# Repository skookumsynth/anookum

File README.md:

# Anookum

The Anookum is a derivative of Olivier Gillet's "Anushri" monophonic synthesizer.

https://github.com/pichenettes/anushri

It uses alternate parts to make sourcing easier for users in North America.
Files are licensed as per the original CC-BY-SA 3.0 license.

No warranties provided.
www.skookumsynth.com

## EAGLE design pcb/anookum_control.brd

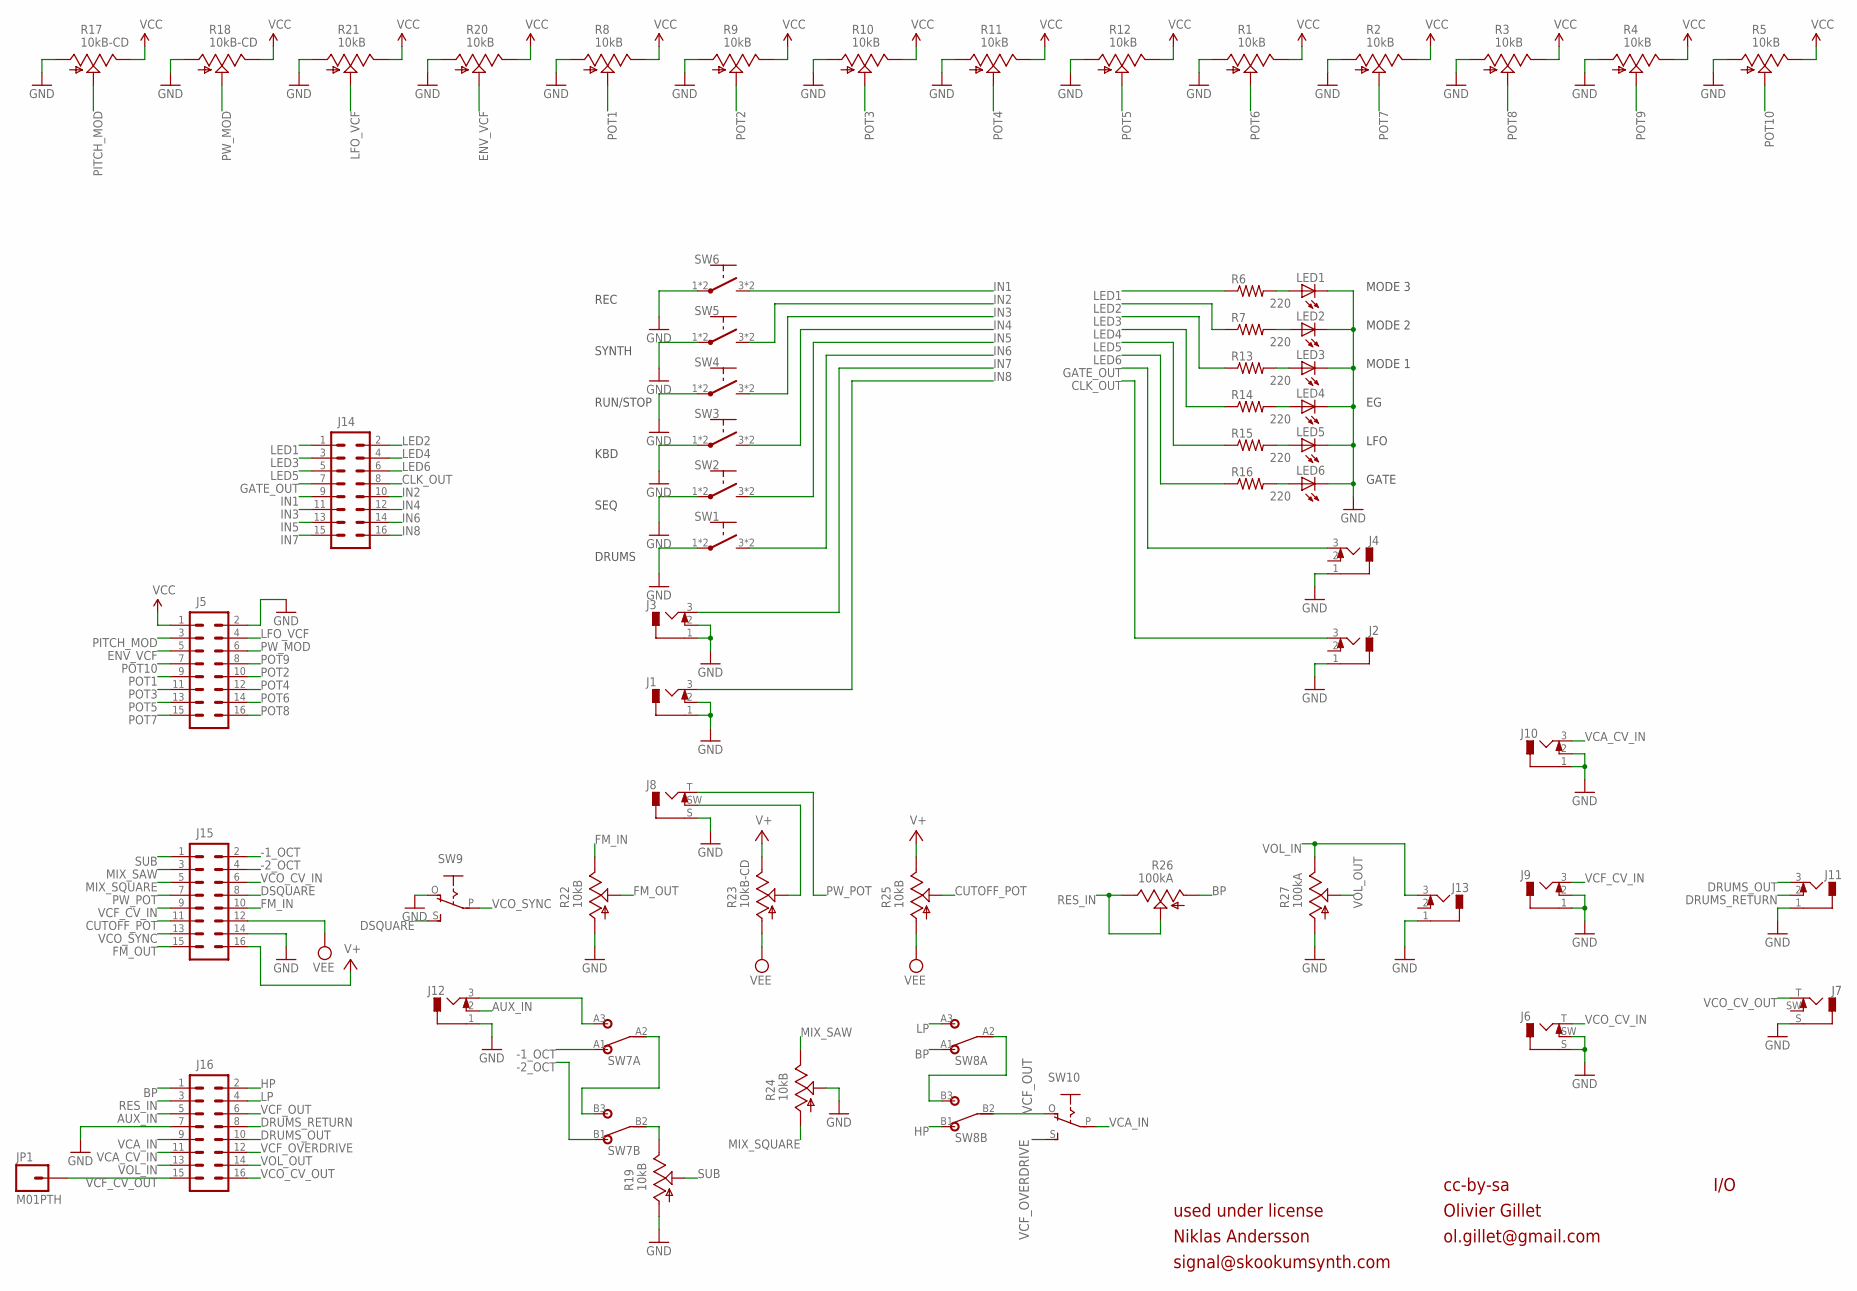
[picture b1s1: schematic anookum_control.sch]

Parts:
J1, J2, J3, J4, J9, J10, J11, J12, J13: JACK_MONO_SW_V; WQP_PJ301M-12@1
J5, J14, J15, J16: M08X2; 2X8
J6, J7, J8: CONN_MONO_SW_F_V; WQP_PJ301M-12
JP1: M01PTH; 1X01
LED1, LED2, LED3, LED4, LED5, LED6: LED3MM
R1, R2, R3, R4, R5, R8, R9, R10, R11, R12, R19, R20, R21, R22, R24, R25: 10kB; ALPS_POT_VERTICAL
R6, R7, R13, R14, R15, R16: 220; 0204/7
R17, R18, R23: 10kB-CD; ALPS_POT_VERTICAL
R26, R27: 100kA; ALPS_POT_VERTICAL
SW1, SW2, SW3, SW4, SW5, SW6: SW_TACTD6; D6
SW7, SW8: DPDT1AD6T2B4M2RE; DPDT
SW9, SW10: EG1218S; EG1218

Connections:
-1_OCT: J15.2, SW7.A1 (1)
-2_OCT: J15.4, SW7.B1 (1)
AUX_IN: J12.2 (SW), J16.5
BP: J16.1, R26.P$3 (A), SW8.A1 (1)
CLK_OUT: J2.3 (T), J14.8
CUTOFF_POT: J15.11, R25.P$2 (S)
DRUMS_OUT: J11.3 (T), J16.10
DRUMS_RETURN: J11.2 (SW), J16.8
DSQUARE: J15.8, SW9.S
ENV_VCF: J5.5, R20.P$2 (S)
FM_IN: J15.10, R22.P$1 (E)
FM_OUT: J15.15, R22.P$2 (S)
GATE_OUT: J4.3 (T), J14.7
GND: J1.1 (S), J1.2 (SW), J2.1 (S), J3.1 (S), J3.2 (SW), J4.1 (S), J5.2, J6.S, J6.SW, J7.S, J8.S, J9.1 (S), J9.2 (SW), J10.1 (S), J10.2 (SW), J11.1 (S), J12.1 (S), J13.1 (S), J15.14, J16.7, LED1.K (C), LED2.K (C), LED3.K (C), LED4.K (C), LED5.K (C), LED6.K (C), R1.P$3 (A), R2.P$3 (A), R3.P$3 (A), R4.P$3 (A), R5.P$3 (A), R8.P$3 (A), R9.P$3 (A), R10.P$3 (A), R11.P$3 (A), R12.P$3 (A), R17.P$3 (A), R18.P$3 (A), R19.P$3 (A), R20.P$3 (A), R21.P$3 (A), R22.P$3 (A), R24.P$2 (S), R27.P$3 (A), SW1.1, SW1.2 (1), SW2.1, SW2.2 (1), SW3.1, SW3.2 (1), SW4.1, SW4.2 (1), SW5.1, SW5.2 (1), SW6.1, SW6.2 (1), SW9.O
HP: J16.2, SW8.B1 (1)
IN1: J14.9, SW6.3 (2), SW6.4 (2)
IN2: J14.10, SW5.3 (2), SW5.4 (2)
IN3: J14.11, SW4.3 (2), SW4.4 (2)
IN4: J14.12, SW3.3 (2), SW3.4 (2)
IN5: J14.13, SW2.3 (2), SW2.4 (2)
IN6: J14.14, SW1.3 (2), SW1.4 (2)
IN7: J3.3 (T), J14.15
IN8: J1.3 (T), J14.16
LED1: J14.1, R6.1
LED2: J14.2, R7.1
LED3: J14.3, R13.1
LED4: J14.4, R14.1
LED5: J14.5, R15.1
LED6: J14.6, R16.1
LFO_VCF: J5.4, R21.P$2 (S)
LP: J16.4, SW8.A3 (3)
MIX_SAW: J15.3, R24.P$1 (E)
MIX_SQUARE: J15.5, R24.P$3 (A)
unnamed: J8.SW, R23.P$2 (S)
unnamed: R19.P$1 (E), SW7.B2 (2)
unnamed: J12.3 (T), SW7.A3 (3)
unnamed: SW8.A2 (2), SW8.B3 (3)
unnamed: LED1.A, R6.2
unnamed: LED2.A, R7.2
unnamed: LED3.A, R13.2
unnamed: LED4.A, R14.2
unnamed: LED5.A, R15.2
unnamed: LED6.A, R16.2
unnamed: SW7.A2 (2), SW7.B3 (3)
PITCH_MOD: J5.3, R17.P$2 (S)
POT1: J5.9, R8.P$2 (S)
POT2: J5.10, R9.P$2 (S)
POT3: J5.11, R10.P$2 (S)
POT4: J5.12, R11.P$2 (S)
POT5: J5.13, R12.P$2 (S)
POT6: J5.14, R1.P$2 (S)
POT7: J5.15, R2.P$2 (S)
POT8: J5.16, R3.P$2 (S)
POT9: J5.8, R4.P$2 (S)
POT10: J5.7, R5.P$2 (S)
PW_MOD: J5.6, R18.P$2 (S)
PW_POT: J8.T, J15.7
RES_IN: J16.3, R26.P$1 (E), R26.P$2 (S)
SUB: J15.1, R19.P$2 (S)
V+: J15.16, R23.P$1 (E), R25.P$1 (E)
VCA_CV_IN: J10.3 (T), J16.11
VCA_IN: J16.9, SW10.P
VCC: J5.1, R1.P$1 (E), R2.P$1 (E), R3.P$1 (E), R4.P$1 (E), R5.P$1 (E), R8.P$1 (E), R9.P$1 (E), R10.P$1 (E), R11.P$1 (E), R12.P$1 (E), R17.P$1 (E), R18.P$1 (E), R20.P$1 (E), R21.P$1 (E)
VCF_CV_IN: J9.3 (T), J15.9
VCF_CV_OUT: J16.15, JP1.1
VCF_OUT: J16.6, SW8.B2 (2), SW10.O
VCF_OVERDRIVE: J16.12, SW10.S
VCO_CV_IN: J6.T, J15.6
VCO_CV_OUT: J7.T, J16.16
VCO_SYNC: J15.13, SW9.P
VEE: J15.12, R23.P$3 (A), R25.P$3 (A)
VOL_IN: J13.3 (T), J16.13, R27.P$1 (E)
VOL_OUT: J16.14, R27.P$2 (S)

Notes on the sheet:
LFO
GATE
MODE 1
MODE 2
MODE 3
cc-by-sa
Olivier Gillet
ol.gillet@gmail.com
I/O
KBD
SEQ
SYNTH
RUN/STOP
REC
DRUMS
used under license
Niklas Andersson
signal@skookumsynth.com

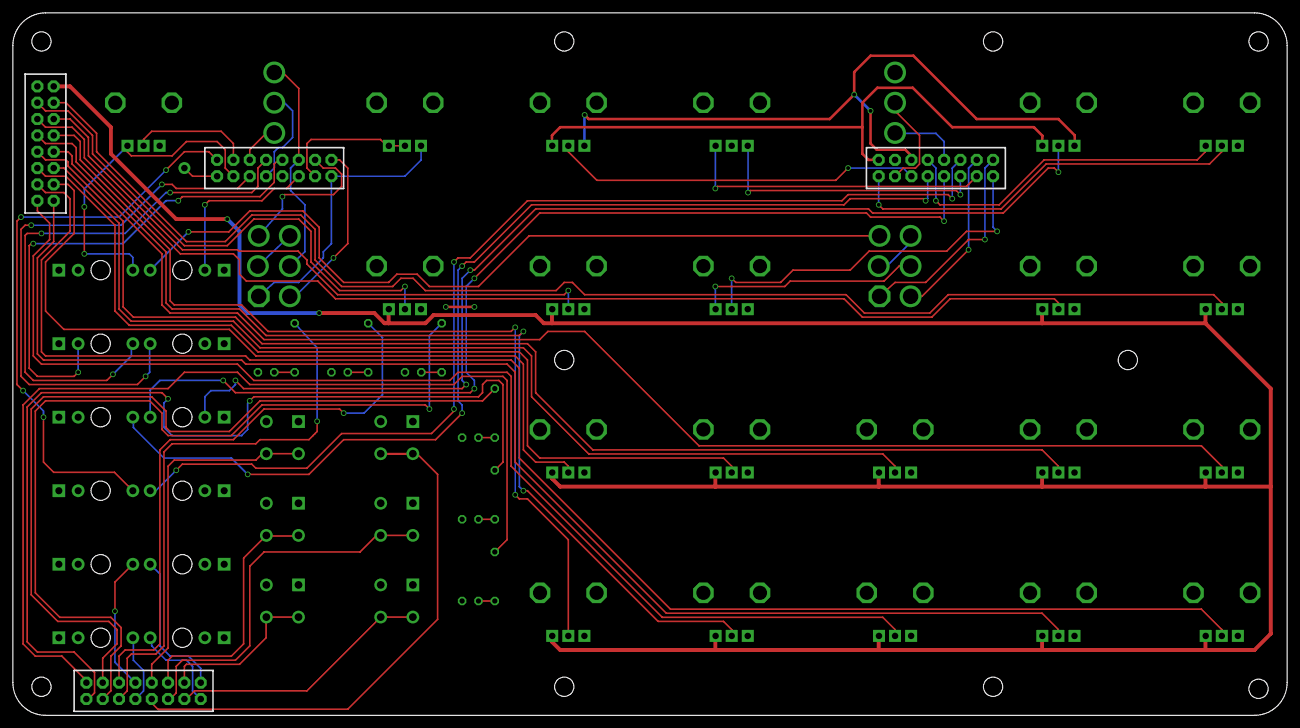
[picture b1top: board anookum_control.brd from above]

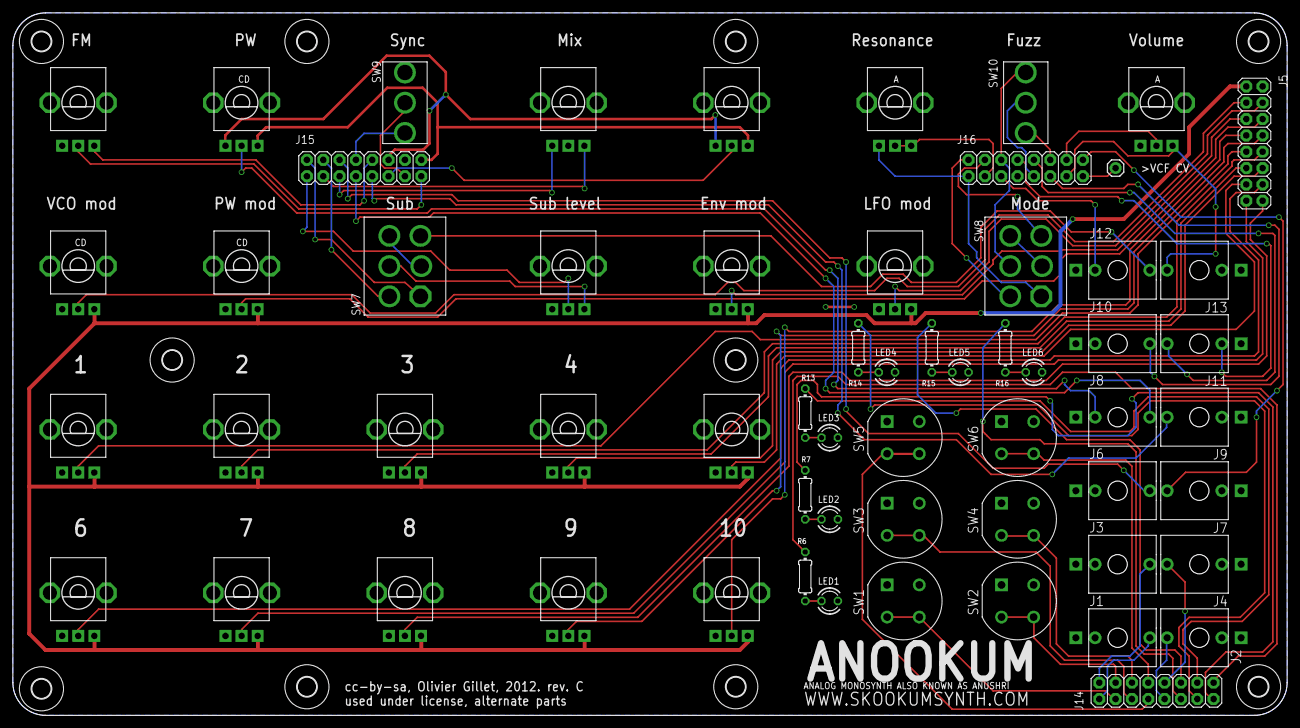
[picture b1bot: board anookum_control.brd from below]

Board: 2 copper layers, 198.1 x 109.2 mm, 70 parts (70 on the bottom side), 73 nets.

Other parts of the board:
U$1, U$2, U$3, U$4, U$6, U$7, U$8, U$9, U$10, U$11: 3,0

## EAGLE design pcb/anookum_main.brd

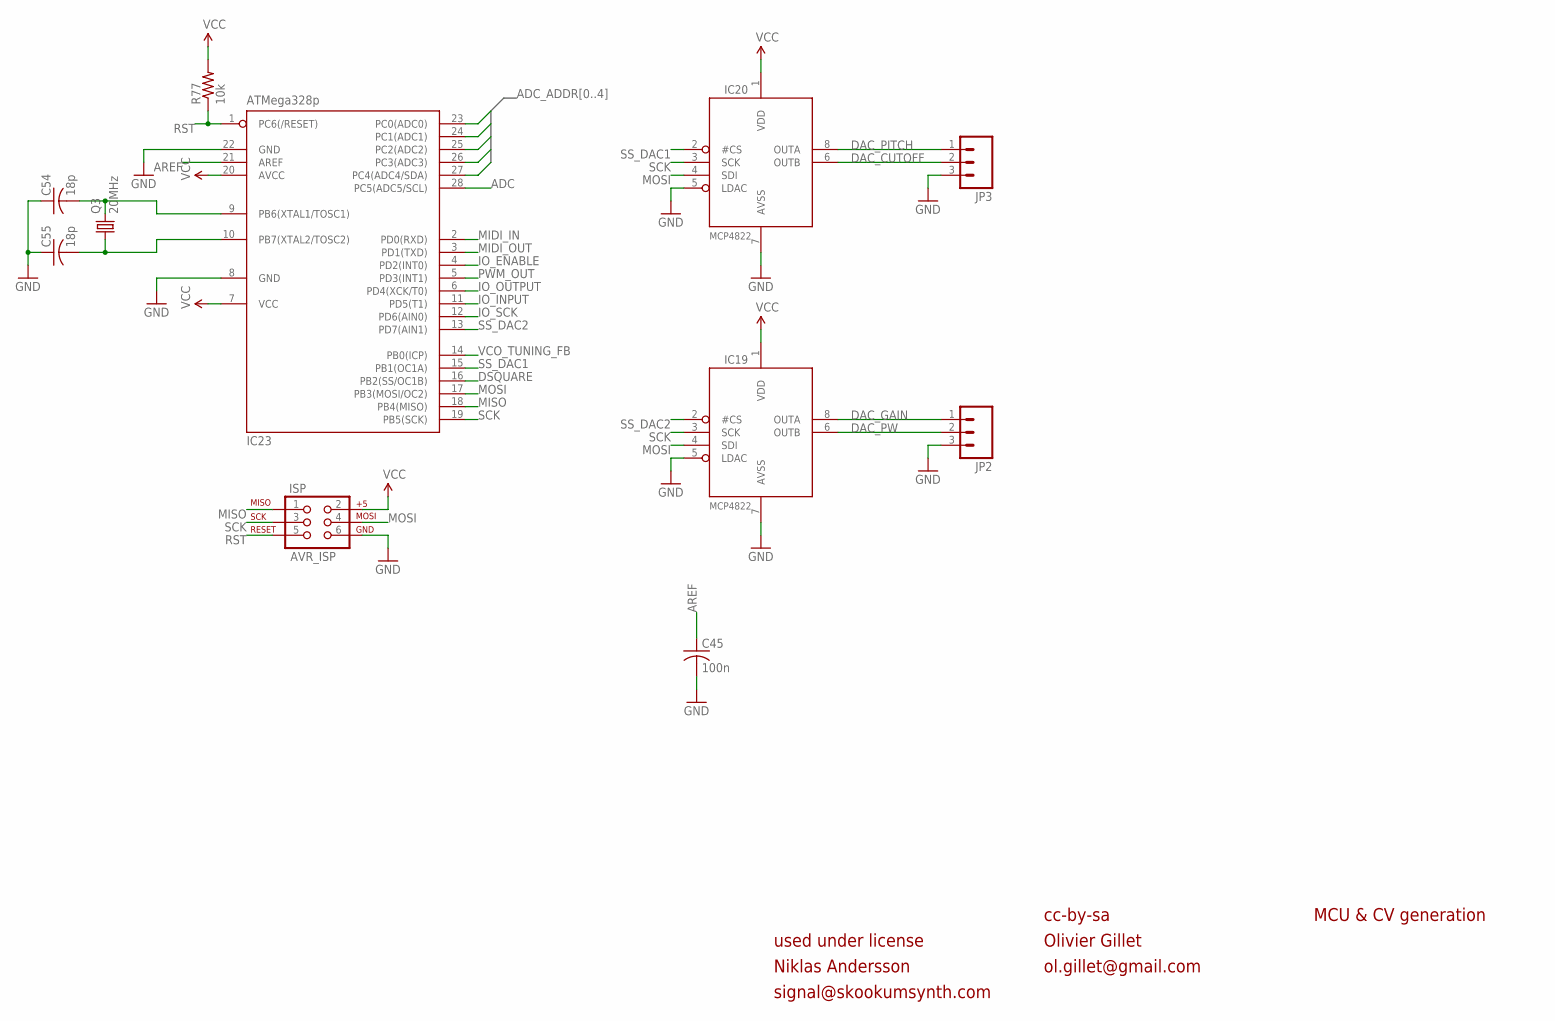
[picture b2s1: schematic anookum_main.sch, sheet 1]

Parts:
C45: 100n; C025-025X050
C54, C55: 18p; C025-025X050
IC19, IC20: MCP4822; DIL08
IC23: ATMega328p; DIL28-3
ISP: AVR_ISP; 2X3
JP2, JP3: M03PTH; 1X03
Q3: 20MHz; HC49U-V
R77: 10k; 0204/7

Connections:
ADC: IC23.28 (PC5(ADC5/SCL)); also elsewhere on the board
ADC_ADDR0: IC23.25 (PC2(ADC2)); also elsewhere on the board
ADC_ADDR1: IC23.24 (PC1(ADC1)); also elsewhere on the board
ADC_ADDR2: IC23.23 (PC0(ADC0)); also elsewhere on the board
ADC_ADDR3: IC23.26 (PC3(ADC3)); also elsewhere on the board
ADC_ADDR4: IC23.27 (PC4(ADC4/SDA)); also elsewhere on the board
AREF: C45.1, IC23.21 (AREF)
DAC_CUTOFF: IC20.6 (OUTB), JP3.2; also elsewhere on the board
DAC_GAIN: IC19.8 (OUTA), JP2.1; also elsewhere on the board
DAC_PITCH: IC20.8 (OUTA), JP3.1; also elsewhere on the board
DAC_PW: IC19.6 (OUTB), JP2.2; also elsewhere on the board
DSQUARE: IC23.16 (PB2(SS/OC1B)); also elsewhere on the board
GND: C45.2, C54.1, C55.1, IC19.5 (LDAC), IC19.7 (AVSS), IC20.5 (LDAC), IC20.7 (AVSS), IC23.8 (GND), IC23.22 (GND), ISP.6, JP2.3, JP3.3; also elsewhere on the board
IO_ENABLE: IC23.4 (PD2(INT0)); also elsewhere on the board
IO_INPUT: IC23.11 (PD5(T1)); also elsewhere on the board
IO_OUTPUT: IC23.6 (PD4(XCK/T0)); also elsewhere on the board
IO_SCK: IC23.12 (PD6(AIN0)); also elsewhere on the board
MIDI_IN: IC23.2 (PD0(RXD)); also elsewhere on the board
MIDI_OUT: IC23.3 (PD1(TXD)); also elsewhere on the board
MISO: IC23.18 (PB4(MISO)), ISP.1
MOSI: IC19.4 (SDI), IC20.4 (SDI), IC23.17 (PB3(MOSI/OC2)), ISP.4
unnamed: C55.2, IC23.10 (PB7(XTAL2/TOSC2)), Q3.1
unnamed: C54.2, IC23.9 (PB6(XTAL1/TOSC1)), Q3.2
PWM_OUT: IC23.5 (PD3(INT1)); also elsewhere on the board
RST: IC23.1 (PC6(/RESET)), ISP.5, R77.1
SCK: IC19.3 (SCK), IC20.3 (SCK), IC23.19 (PB5(SCK)), ISP.3
SS_DAC1: IC20.2 (#CS), IC23.15 (PB1(OC1A))
SS_DAC2: IC19.2 (#CS), IC23.13 (PD7(AIN1))
VCC: IC19.1 (VDD), IC20.1 (VDD), IC23.7 (VCC), IC23.20 (AVCC), ISP.2, R77.2; also elsewhere on the board
VCO_TUNING_FB: IC23.14 (PB0(ICP)); also elsewhere on the board

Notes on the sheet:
cc-by-sa
Olivier Gillet
ol.gillet@gmail.com
MCU & CV generation
used under license
Niklas Andersson
signal@skookumsynth.com

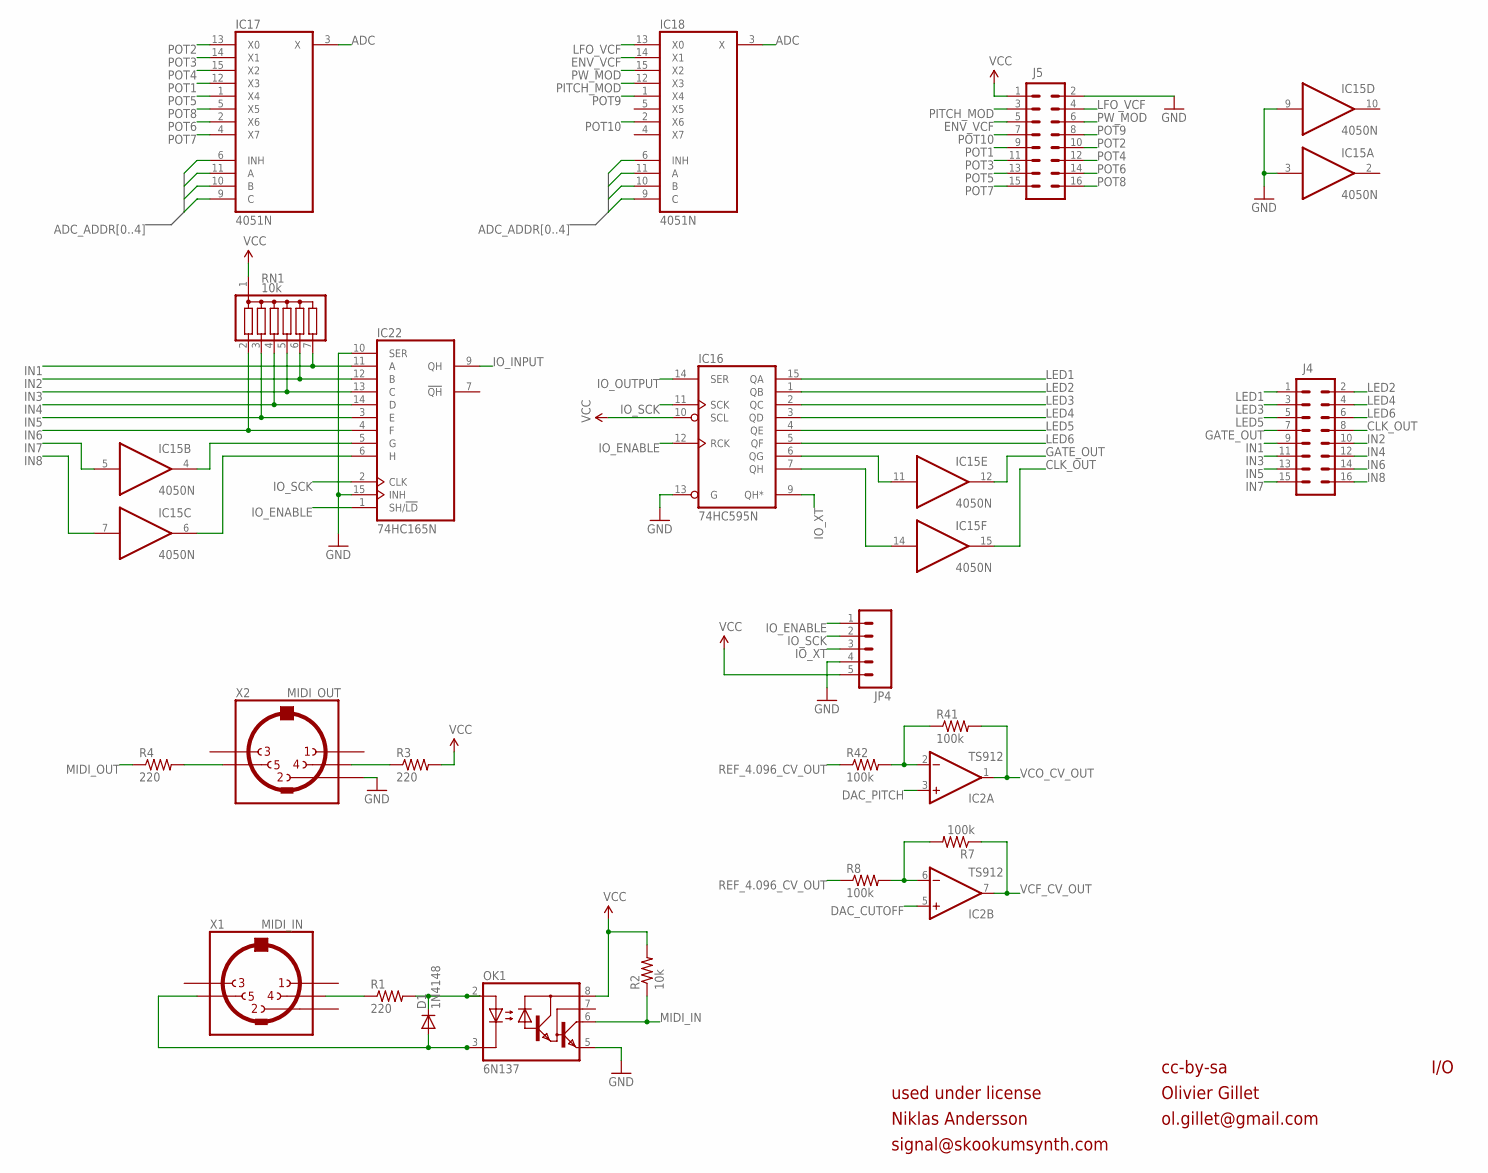
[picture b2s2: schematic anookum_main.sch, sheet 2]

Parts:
D1: 1N4148; D-5
IC2: TS912; DIL08
IC15: 4050N; DIL16
IC16: 74HC595N; DIL16
IC17, IC18: 4051N; DIL16
IC22: 74HC165N; DIL16
J4, J5: M08X2; 2X8
JP4: M05PTH; 1X05
OK1: 6N137; DIL08
R1, R3, R4: 220; 0204/7
R2: 10k; 0204/7
R7, R8, R41, R42: 100k; 0204/7
RN1: 10k; SIL7
X1: MIDI_IN; SDS-50J
X2: MIDI_OUT; SDS-50J

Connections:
ADC: IC17.3 (X), IC18.3 (X); also elsewhere on the board
ADC_ADDR0: IC17.11 (A), IC18.11 (A); also elsewhere on the board
ADC_ADDR1: IC17.10 (B), IC18.10 (B); also elsewhere on the board
ADC_ADDR2: IC17.9 (C), IC18.9 (C); also elsewhere on the board
ADC_ADDR3: IC17.6 (INH); also elsewhere on the board
ADC_ADDR4: IC18.6 (INH); also elsewhere on the board
CLK_OUT: IC15.15 (O), J4.8
DAC_CUTOFF: IC2.5 (+IN); also elsewhere on the board
DAC_PITCH: IC2.3 (+IN); also elsewhere on the board
ENV_VCF: IC18.14 (X1), J5.5
GATE_OUT: IC15.12 (O), J4.7
GND: IC15.3 (I), IC15.9 (I), IC16.13 (G), IC22.10 (SER), IC22.15 (INH), J5.2, JP4.4, OK1.5 (GND), X2.2; also elsewhere on the board
IN1: IC22.11 (A), J4.9, RN1.7
IN2: IC22.12 (B), J4.10, RN1.6
IN3: IC22.13 (C), J4.11, RN1.5
IN4: IC22.14 (D), J4.12, RN1.4
IN5: IC22.3 (E), J4.13, RN1.3
IN6: IC22.4 (F), J4.14, RN1.2
IN7: IC15.5 (I), J4.15
IN8: IC15.7 (I), J4.16
IO_ENABLE: IC16.12 (RCK), IC22.1 (SH/!LD), JP4.1; also elsewhere on the board
IO_INPUT: IC22.9 (QH); also elsewhere on the board
IO_OUTPUT: IC16.14 (SER); also elsewhere on the board
IO_SCK: IC16.11 (SCK), IC22.2 (CLK), JP4.2; also elsewhere on the board
IO_XT: IC16.9 (QH*), JP4.3
LED1: IC16.15 (QA), J4.1
LED2: IC16.1 (QB), J4.2
LED3: IC16.2 (QC), J4.3
LED4: IC16.3 (QD), J4.4
LED5: IC16.4 (QE), J4.5
LED6: IC16.5 (QF), J4.6
LFO_VCF: IC18.13 (X0), J5.4
MIDI_IN: OK1.6 (VO), R2.1; also elsewhere on the board
MIDI_IN4: R1.1, X1.4
MIDI_IN5: D1.A, OK1.3 (C), X1.5
MIDI_OUT: R4.1; also elsewhere on the board
MIDI_OUT3: R3.1, X2.4
MIDI_OUT5: R4.2, X2.5
unnamed: IC15.11 (I), IC16.6 (QG)
unnamed: IC15.14 (I), IC16.7 (QH)
unnamed: D1.C, OK1.2 (A), R1.2
unnamed: IC15.4 (O), IC22.5 (G)
unnamed: IC15.6 (O), IC22.6 (H)
unnamed: IC2.2 (-IN), R41.1, R42.2
unnamed: IC2.6 (-IN), R7.2, R8.2
PITCH_MOD: IC18.12 (X3), J5.3
POT1: IC17.12 (X3), J5.9
POT2: IC17.13 (X0), J5.10
POT3: IC17.14 (X1), J5.11
POT4: IC17.15 (X2), J5.12
POT5: IC17.1 (X4), J5.13
POT6: IC17.2 (X6), J5.14
POT7: IC17.4 (X7), J5.15
POT8: IC17.5 (X5), J5.16
POT9: IC18.1 (X4), J5.8
POT10: IC18.2 (X6), J5.7
PW_MOD: IC18.15 (X2), J5.6
REF_4.096_CV_OUT: R8.1, R42.1; also elsewhere on the board
VCC: IC16.10 (SCL), J5.1, JP4.5, OK1.8 (VCC), R2.2, R3.2, RN1.1; also elsewhere on the board
VCF_CV_OUT: IC2.7 (OUT), R7.1; also elsewhere on the board
VCO_CV_OUT: IC2.1 (OUT), R41.2; also elsewhere on the board

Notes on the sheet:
cc-by-sa
Olivier Gillet
ol.gillet@gmail.com
I/O
used under license
Niklas Andersson
signal@skookumsynth.com

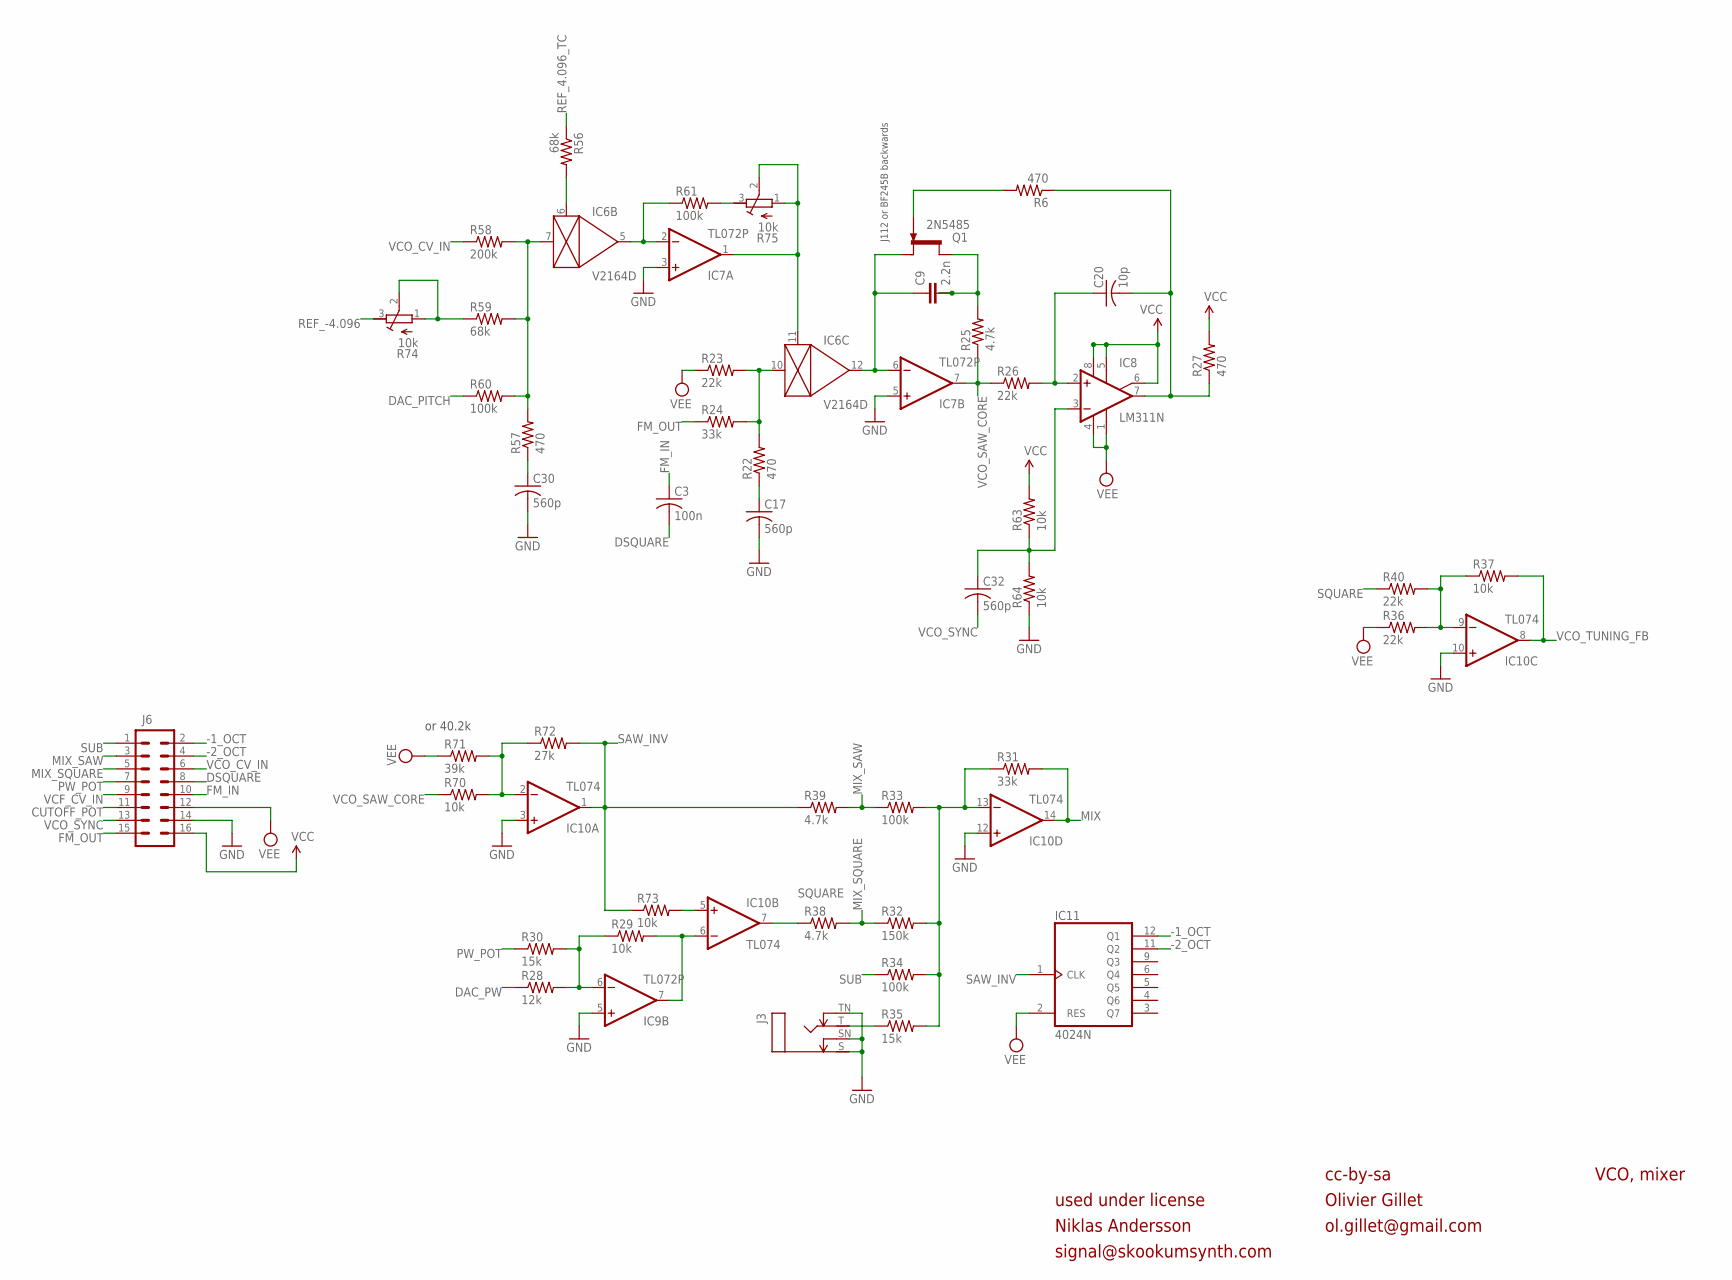
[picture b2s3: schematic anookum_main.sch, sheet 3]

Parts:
C3: 100n; C025-025X050
C9: 2.2n; C2.5/5-5
C17, C30, C32: 560p; C025-025X050
C20: 10p; C025-025X050
IC6: V2164D; DIL16
IC7, IC9: TL072P; DIL08
IC8: LM311N; DIL08
IC10: TL074; DIL14
IC11: 4024N; DIL14
J3: MONOSWSLIM; NRJ4HF
J6: M08X2; 2X8
Q1: 2N5485; TO92-
R6, R22, R27, R57: 470; 0204/7
R23, R26, R36, R40: 22k; 0204/7
R24, R31: 33k; 0204/7
R25, R38, R39: 4.7k; 0204/7
R28: 12k; 0204/7
R29, R37, R63, R64, R70, R73: 10k; 0204/7
R30, R35: 15k; 0204/7
R32: 150k; 0204/7
R33, R34, R60, R61: 100k; 0204/7
R56, R59: 68k; 0204/7
R58: 200k; 0204/7
R71: 39k; 0204/7
R72: 27k; 0204/7
R74, R75: 10k; RTRIM3296W

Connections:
-1_OCT: IC11.12 (Q1), J6.2
-2_OCT: IC11.11 (Q2), J6.4
CUTOFF_POT: J6.11; also elsewhere on the board
DAC_PITCH: R60.1; also elsewhere on the board
DAC_PW: R28.1; also elsewhere on the board
DSQUARE: C3.2, J6.8; also elsewhere on the board
FM_IN: C3.1, J6.10; also elsewhere on the board
FM_OUT: J6.15, R24.1
GND: C17.2, C30.2, IC7.3 (+IN), IC7.5 (+IN), IC9.5 (+IN), IC10.3 (+IN), IC10.10 (+IN), IC10.12 (+IN), J3.S, J3.SN, J3.TN, J6.14, R64.1; also elsewhere on the board
MIX: IC10.14 (OUT), R31.2; also elsewhere on the board
MIX_SAW: J6.3, R33.1, R39.2
MIX_SQUARE: J6.5, R32.1, R38.2
unnamed: IC6.11 (CTRL), IC7.1 (OUT), R75.1 (E), R75.2 (S)
unnamed: C20.2, IC8.7 (OUT), R6.1, R27.1
unnamed: R61.2, R75.3 (A)
unnamed: Q1.1 (G), R6.2
unnamed: J3.T, R35.1
unnamed: R59.1, R74.1 (E), R74.2 (S)
unnamed: C9.1, IC6.12 (OUT), IC7.6 (-IN), Q1.2 (S)
unnamed: C32.1, IC8.3 (-IN), R63.1, R64.2
unnamed: IC6.6 (CTRL), R56.2
unnamed: IC9.6 (-IN), R28.2, R29.1, R30.2
unnamed: IC6.7 (IN), R57.2, R58.2, R59.2, R60.2
unnamed: C30.1, R57.1
unnamed: IC6.5 (OUT), IC7.2 (-IN), R61.1
unnamed: IC6.10 (IN), R22.2, R23.2, R24.2
unnamed: C17.1, R22.1
unnamed: IC9.7 (OUT), IC10.6 (-IN), R29.2
unnamed: IC10.2 (-IN), R70.2, R71.2, R72.1
unnamed: C20.1, IC8.2 (+IN), R26.2
unnamed: IC10.5 (+IN), R73.2
unnamed: IC10.9 (-IN), R36.2, R37.1, R40.2
unnamed: IC10.13 (-IN), R31.1, R32.2, R33.2, R34.2, R35.2
PW_POT: J6.7, R30.1
REF_4.096_TC: R56.1; also elsewhere on the board
REF_-4.096: R74.3 (A); also elsewhere on the board
SAW_INV: IC10.1 (OUT), IC11.1 (CLK), R39.1, R72.2, R73.1
SQUARE: IC10.7 (OUT), R38.1, R40.1
SUB: J6.1, R34.1
VCC: IC8.5 (ON), IC8.6 (ON/STR), IC8.8 (V+), J6.16, R27.2, R63.2; also elsewhere on the board
VCF_CV_IN: J6.9; also elsewhere on the board
VCO_CV_IN: J6.6, R58.1
VCO_RAMP: C9.2, C9.3, Q1.3 (D), R25.2
VCO_SAW_CORE: IC7.7 (OUT), R25.1, R26.1, R70.1
VCO_SYNC: C32.2, J6.13
VCO_TUNING_FB: IC10.8 (OUT), R37.2; also elsewhere on the board
VEE: IC8.1 (GND), IC8.4 (V-), IC11.2 (RES), J6.12, R23.1, R36.1, R71.1; also elsewhere on the board

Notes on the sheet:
cc-by-sa
Olivier Gillet
ol.gillet@gmail.com
VCO, mixer
or 40.2k
J112 or BF245B backwards
used under license
Niklas Andersson
signal@skookumsynth.com

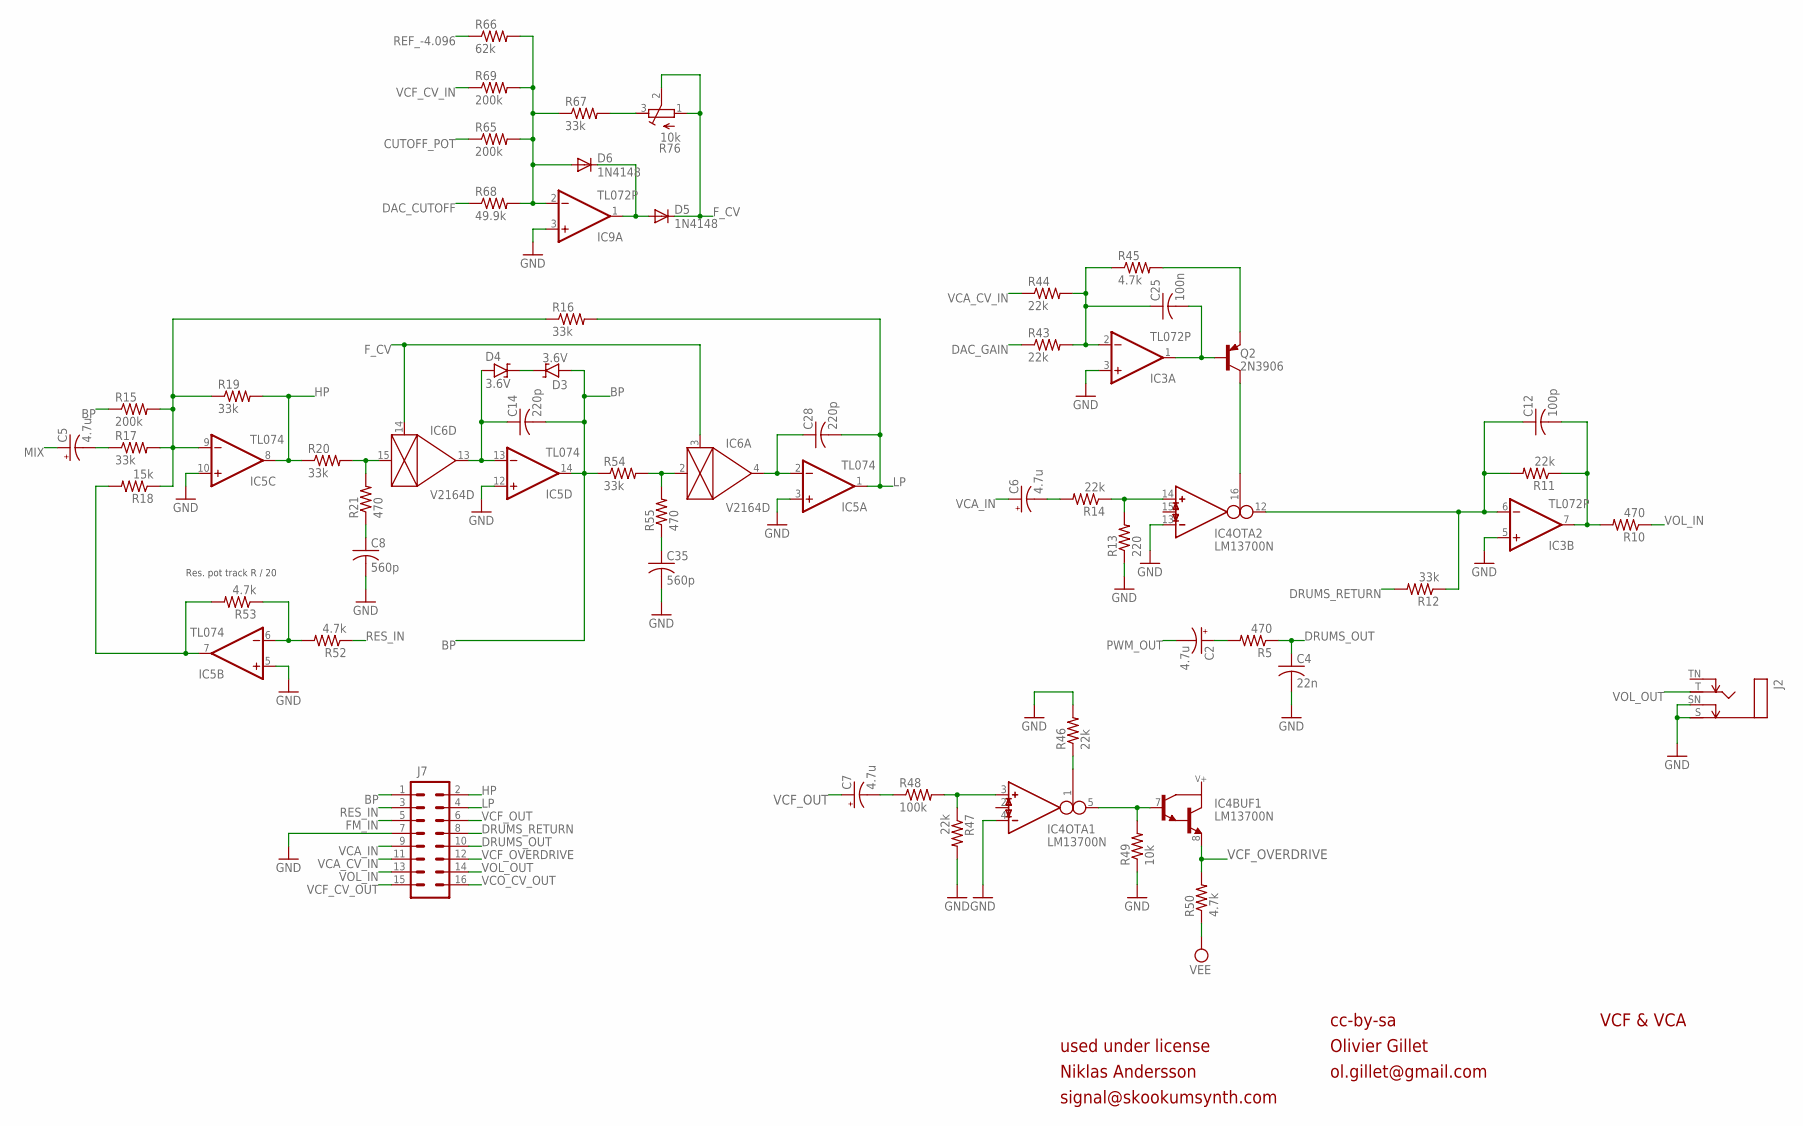
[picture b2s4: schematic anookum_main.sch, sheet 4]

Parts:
C2, C5, C6, C7: 4.7u; E2,5-6
C4: 22n; C050-030X075
C8, C35: 560p; C025-025X050
C12: 100p; C025-025X050
C14, C28: 220p; C025-025X050
C25: 100n; C025-025X050
D3, D4: 3.6V; D-5
D5, D6: 1N4148; D-5
IC3, IC9: TL072P; DIL08
IC4: LM13700N; DIL16
IC5: TL074; DIL14
IC6: V2164D; DIL16
J2: MONOSWSLIM; NRJ4HF
J7: M08X2; 2X8
Q2: 2N3906; TO92-
R5, R10, R21, R55: 470; 0204/7
R11, R14, R43, R44, R46, R47: 22k; 0204/7
R12, R16, R17, R19, R20, R54, R67: 33k; 0204/7
R13: 220; 0204/7
R15, R65, R69: 200k; 0204/7
R18: 15k; 0204/7
R45, R50, R52, R53: 4.7k; 0204/7
R48: 100k; 0204/7
R49: 10k; 0204/7
R66: 62k; 0204/7
R68: 49.9k; 0204/7
R76: 10k; RTRIM3296W

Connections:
BP: C14.2, D3.A, IC5.14 (OUT), J7.1, R15.1, R54.1
CUTOFF_POT: R65.1; also elsewhere on the board
DAC_CUTOFF: R68.1; also elsewhere on the board
DAC_GAIN: R43.1; also elsewhere on the board
DRUMS_OUT: C4.1, J7.10, R5.1
DRUMS_RETURN: J7.8, R12.2
FM_IN: J7.5; also elsewhere on the board
F_CV: D5.C, IC6.3 (CTRL), IC6.14 (CTRL), R76.1 (E), R76.2 (S)
GND: C4.2, C8.2, C35.2, IC3.3 (+IN), IC3.5 (+IN), IC4.4 (IN_N), IC4.13 (IN_N), IC5.3 (+IN), IC5.5 (+IN), IC5.10 (+IN), IC5.12 (+IN), IC9.3 (+IN), J2.S, J2.SN, J7.7, R13.1, R46.2, R47.2, R49.1; also elsewhere on the board
HP: IC5.8 (OUT), J7.2, R19.2, R20.1
LP: C28.2, IC5.1 (OUT), J7.4, R16.2
MIX: C5.+; also elsewhere on the board
unnamed: C2.+, R5.2
unnamed: IC5.9 (-IN), R15.2, R16.1, R17.2, R18.1, R19.1
unnamed: C28.1, IC5.2 (-IN), IC6.4 (OUT)
unnamed: C8.1, R21.1
unnamed: IC5.6 (-IN), R52.2, R53.1
unnamed: IC5.7 (OUT), R18.2, R53.2
unnamed: C5.-, R17.1
unnamed: C35.1, R55.1
unnamed: C14.1, D4.A, IC5.13 (-IN), IC6.13 (OUT)
unnamed: R67.2, R76.3 (A)
unnamed: IC4.16 (I_BIAS), Q2.1 (C)
unnamed: IC6.2 (IN), R54.2, R55.2
unnamed: C7.-, R48.1
unnamed: IC6.15 (IN), R20.2, R21.2
unnamed: C6.-, R14.2
unnamed: D5.A, D6.C, IC9.1 (OUT)
unnamed: Q2.3 (E), R45.2
unnamed: D6.A, IC9.2 (-IN), R65.2, R66.2, R67.1, R68.2, R69.2
unnamed: C25.2, IC3.1 (OUT), Q2.2 (B)
unnamed: IC4.14 (IN_P), R13.2, R14.1
unnamed: D3.C, D4.C
unnamed: C12.2, IC3.7 (OUT), R10.2, R11.1
unnamed: C12.1, IC3.6 (-IN), IC4.12 (OUT), R11.2, R12.1
unnamed: IC4.1 (I_BIAS), R46.1
unnamed: IC4.3 (IN_P), R47.1, R48.2
unnamed: IC4.5 (OUT), IC4.7 (B), R49.2
unnamed: C25.1, IC3.2 (-IN), R43.2, R44.2, R45.1
PWM_OUT: C2.-; also elsewhere on the board
REF_-4.096: R66.1; also elsewhere on the board
RES_IN: J7.3, R52.1
VCA_CV_IN: J7.11, R44.1
VCA_IN: C6.+, J7.9
VCF_CV_IN: R69.1; also elsewhere on the board
VCF_CV_OUT: J7.15; also elsewhere on the board
VCF_OUT: C7.+, J7.6
VCF_OVERDRIVE: IC4.8 (E), J7.12, R50.2
VCO_CV_OUT: J7.16; also elsewhere on the board
VEE: R50.1; also elsewhere on the board
VOL_IN: J7.13, R10.1
VOL_OUT: J2.T, J7.14

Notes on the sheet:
Res. pot track R / 20
cc-by-sa
Olivier Gillet
ol.gillet@gmail.com
VCF & VCA
used under license
Niklas Andersson
signal@skookumsynth.com

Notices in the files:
pcb/anookum_control.brd:
cc-by-sa, Olivier Gillet, 2012. rev. C
used under license, alternate parts
